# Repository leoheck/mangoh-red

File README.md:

# MangOH Red

[MangOH Red](https://mangoh.io/mangoh-red-resources) board was build using Mentor DxDesigner for schematics and Pantheon PCB for layouts. This project aims to build a version using the GREAT [Kicad](http://kicad-pcb.org/) and [FreeCad](https://www.freecadweb.org/) with [StepUp](http://kicad-pcb.org/external-tools/stepup/) plugin for Kicad.

_This project is a work in progress._

Current status
- [x] [Schematics](https://github.com/leoheck/mangoh-red/blob/master/mangoh-red.pdf)
- [x] Footprint associations (100%)
- [ ] Fix some footprints (80%)
- [x] Footprint placement (100%)
- [x] 3D models associations (90%)
- [ ] Missing 3D models creation
- [x] PCB form factor
- [ ] Routing
- [x] Bill of materials
- [ ] GERBERS

Current board and 3d view

*Feel free to help me with a PR :)*

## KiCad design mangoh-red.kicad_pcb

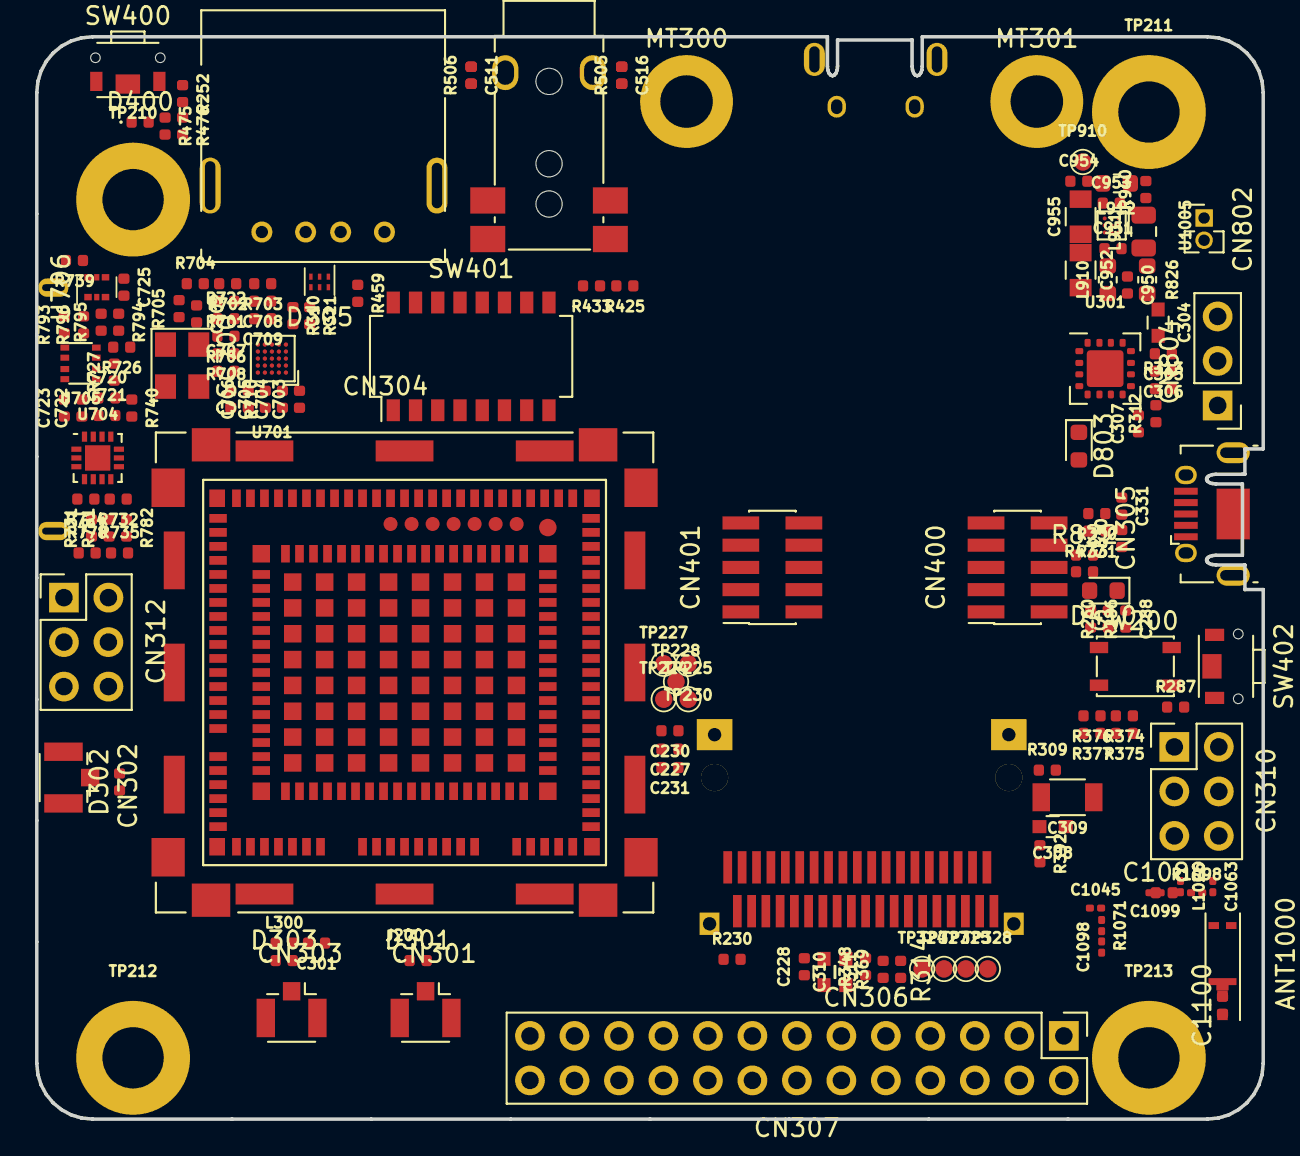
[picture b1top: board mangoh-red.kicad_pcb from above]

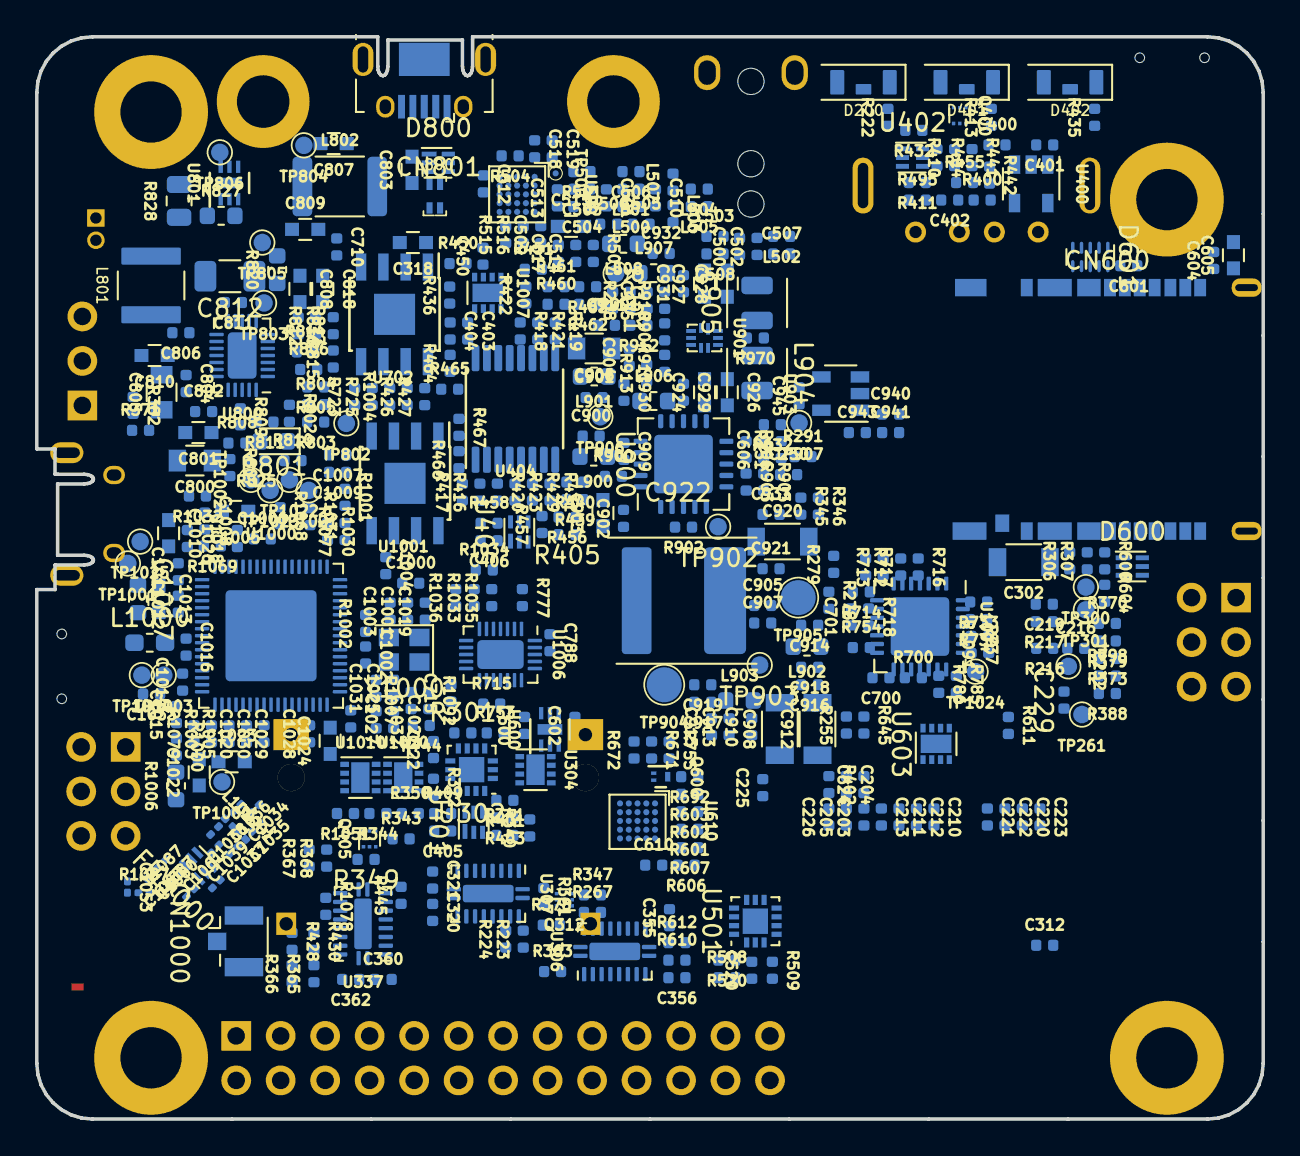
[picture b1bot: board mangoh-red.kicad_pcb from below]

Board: 6 copper layers, 70.0 x 61.8 mm, 598 parts (443 on the bottom side), 364 nets, no tracks yet.

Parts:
ANT1000: WLA.01
C203, C204, C205, C210, C211, C212, C213, C220, C221, C222, C223, C225, C226, C227, C228, C229, C230, C231, C312, C507, C508: 22p; C_0402_1005Metric
C216, C219: 12p; C_0402_1005Metric
C250, C606: 1n; C_0402_1005Metric
C288, C305, C307, C320, C321, C322, C355, C356, C360, C362, C400, C401, C402, C403, C404, C405, C406, C450, C517, C518, C520, C604, C610, C624, C700, C701, C702, C704, C705, C715, C720, C721, C722, C723, C725, C900, C901, C902, C904, C905, C907, C910, C913, C914, C915, C916, C917, C918, C919, C921, C929, C930, C931, C932, C933, C940, C941, C950, C951, C953, C954, C1000, C1003, C1007, C1012, C1014, C1020: 100n; C_0402_1005Metric
C301: 15p; C_0402_1005Metric
C302, C309, C908, C912, C920: 47u; C_1206_3216Metric
C304: 1u; C_0603_1608Metric
C306, C509, C512, C513, C514, C519, C703, C706, C707, C708, C709, C788, C1008, C1009, C1025: 4.7u; C_0402_1005Metric
C308, C605, C810: 4.7u; C_0603_1608Metric
C310, C311, C318, C803, C808, C818, C903, C1005, C1013, C1017: 10u; C_0603_1608Metric
C330, C331: 47p; C_0402_1005Metric
C500, C501, C502, C505, C506, C510, C511, C516, C1006, C1019, C1026, C1030, C1033: 100p; C_0402_1005Metric
C503, C504, C600, C601, C602, C710, C802, C804, C943, C945, C1011, C1016, C1018, C1021, C1032: 1u; C_0402_1005Metric
C515, C1010, C1022, C1023, C1024: 2.2u; C_0603_1608Metric
C800: 22u; C_0805_2012Metric
C801, C807, C809: 220n; C_0603_1608Metric
C805, C906, C952, C955: 10u; C_0805_2012Metric
C806, C909: 47n; C_0402_1005Metric
C811: 10u; C_0402_1005Metric
C812: 10u; C_1206_3216Metric
C911: 10n; C_0402_1005Metric
C922: 1.5m; CAP_2P_0720x0630_POL_NIB
C924, C926, C927, C928: 22u; C_0603_1608Metric
C925: 56p; C_0402_1005Metric
C1001, C1004: 470n; C_0402_1005Metric
C1002, C1027, C1028, C1029, C1031, C1100: 10p; C_0402_1005Metric
C1015: 470p; C_0402_1005Metric
C1034: 1p; C_0201_0603Metric
C1035, C1036, C1039, C1053, C1065: 1.5p; C_0201_0603Metric
C1037, C1038: 1.8p; C_0201_0603Metric
C1045, C1063, C1098, C1099: 10p; C_0201_0603Metric
C1060: 2.7p; C_0201_0603Metric
C1061: 100p; C_0201_0603Metric
C1087: 2.2p; C_0201_0603Metric
C1088: 10k; R_0402_1005Metric
CN301, CN302, CN303, CN1000: uFL; CONN_3P_0300x0310_RF_HIROSE
CN304: USB_A; CONN_4P_1450x1400_USB_2GND_RA_THRU
CN305, CN801: USB_B_Micro; CONN_5P_0750x0560_USB_5GND_HRS_ZX62RD
CN306: Conn_02x19_Counter_Clockwise; CONN_38P_1820x1150_0080CC_EVERCLEAR
CN307: Conn_02x13_Odd_Even; CONN_26P_3300x0483_0254CC_HEADER_THRU
CN310, CN312: Conn_02x03_Odd_Even; CONN_6P_0760x0510_HEADER_THRU_0254CC
CN400, CN401: Conn_02x05_Odd_Even; CONN_10P_0673x0305_0127CC_SMT
CN500: JP036-RT3B4AB; CONN_6P_1480x0640_AUDIO_JACK_DUAL
CN600: CN600; CONN_25P_1780x1290_0088CC_MICROSDSIM
CN802: Conn_01x02; CONN_2P_0590x0450_0200CC_THRU_HEADER
CN804: Conn_01x03; CONN_3P_0762x0254_VERTICAL_HEADER_SINGLE_ROW_THRU_SAMTEC_TSW
D200, D401, D402: LED_PAD; 12-21SYGC_S530-E2_TR8
D301, D302, D303: 0.05p; LED_0402_1005Metric
D305, D800: TPD4S012DRYR; DFN_6P_0145x0100_0050CC
D400: D_TVS; LED_0402_1005Metric
D410, D801, D803: LED; LED_0603_1608Metric
D600: RCLAMP0503N; DFN_6P_0145x0100_0050CC
D601: TPD6E004RSER; QFN_8P_0150x0150_0050CC
FIL1000: BL1608-05A2450TB; FIL_6P_0160x0080_0050CC_MURATA
J200: CF3-Socket; SIERRA_WP_SNAP-IN_BASE
L300: 47n; L_0402_1005Metric
L500, L501, L504, L505, L506, L507: 0; L_0402_1005Metric
L502, L503: 22n; L_0402_1005Metric
L508, L900, L901, L902, L903, L906, L907, L910, L912: 0; L_0603_1608Metric
L800: TCM1210-900-2P-T000; EXC24C
L801: 3.3u; IND_2P_0400x0400_0237CC_COILCRAFT
L802: 0; L_1812_4532Metric
L904, L905: 2.2u; 2016L
L911: 0; L_0805_2012Metric
L1000: 2.2u; L_0603_1608Metric_Pad1.05x0.95mm_HandSolder
L1001, L1002: 1.2n; L_0201_0603Metric
L1026: 2.2n; L_0201_0603Metric
L1087: 2.4n; L_0201_0603Metric
MT300, MT301: Round_Standoff_M2; STANDOFF_0530_0300H_THRU
OSC700: ENE3687A; Crystal_SMD_SeikoEpson_FA238V-4Pin_3.2x2.5mm
Q312, Q400, Q405: NSBC114YDP6T5G; SOT963_6P_0100x0080_0035CC
Q600: PDTC115EM; DFN_3P_0060x0100_0035CC
R216, R217, R223, R224, R230, R238, R252, R255, R260, R267, R278, R279, R309, R340, R341, R343, R344, R345, R346, R347, R348, R350, R363, R365, R366, R367, R368, R369, R370, R371, R373, R374, R375, R382, R392, R400, R416, R417, R418, R426, R427, R439, R440, R441, R442, R460, R461, R464, R465, R467, R475, R495, R505, R506, R507, R515, R516, R610, R611, R612, R645, R725, R732, R733, R736, R737, R739, R753, R754, R755, R778, R782, R785, R786, R793, R794, R795, R796, R798, R825, R902, R903, R940, R970, R1068, R1078, R1091, R1092: 0; R_0402_1005Metric
R222: 280; R_0402_1005Metric
R251, R291, R402, R432, R632: 100k; R_0402_1005Metric
R286, R301, R306, R312, R313, R372, R376, R377, R379, R388, R404, R411, R422, R425, R433, R436, R450, R451, R462, R463, R508, R509, R520, R671, R672, R692, R700, R701, R702, R703, R704, R705, R706, R708, R712, R713, R714, R715, R716, R717, R718, R722, R724, R726, R727, R731, R740, R744, R777, R781, R802, R803, R804, R805, R806, R807, R808, R809, R810, R811, R812, R904, R1000, R1001, R1002, R1003, R1004, R1005, R1051, R1077, R1079: 10k; R_0402_1005Metric
R287, R410, R445, R459: 100; R_0402_1005Metric
R307: 220; R_0402_1005Metric
R310, R311: 22; R_0402_1005Metric
R314, R401, R403, R455, R456, R457, R476, R601, R602, R603, R606, R607, R1033, R1034: 47k; R_0402_1005Metric
R330, R331: 27; R_0402_1005Metric
R349, R361, R378, R910: 820k; R_0402_1005Metric
R405, R413, R435, R477: 820; R_0402_1005Metric
R409, R458: 330; R_0402_1005Metric
R419, R420, R421, R423, R428, R429, R430, R431, R466: 4.7k; R_0402_1005Metric
R500, R501: 2.2k; R_0402_1005Metric
R504: 20K; R_0402_1005Metric
R600, R1035, R1036: 33; R_0402_1005Metric
R604, R813: 15k; R_0402_1005Metric
R710: 12k; R_0402_1005Metric
R723, R735, R1030, R1031, R1032, R1069: 10K; R_0402_1005Metric
R814: 150; R_0402_1005Metric
R815: 30.1k; R_0402_1005Metric
R816: 5.23k; R_0402_1005Metric
R820, R826, R827, R1006: 0; R_0603_1608Metric
R822, R901: R; R_0402_1005Metric
R828: 68m; R_0805_2012Metric
R900, R906: 33k; R_0402_1005Metric
R905: 220k; R_0402_1005Metric
R911: 360k; R_0402_1005Metric
R912, R913: 180k; R_0402_1005Metric
R1007: 36; R_0402_1005Metric
R1071, R1087: 10k; R_0201_0603Metric
R1098: 2.7p; R_0201_0603Metric
SW200: PTS810; SW_SPST_PTS810
SW400, SW402: SKTDLDE010; SW_5P_0390x0290_0280CC_THRU_2P
SW401: Conn_02x08_Counter_Clockwise; SW_16P_1128x0620_0127CC_DIP_SPST
TP210, TP211, TP212, TP213: TESTPOINT_0650_RND_0350H; Test_Point_Pad_d_0650
TP224, TP225, TP227, TP228, TP230, TP232, TP261, TP300, TP301, TP324, TP325, TP327, TP328, TP802, TP803, TP804, TP805, TP806, TP901, TP902, TP903, TP906, TP907, TP910, TP1000, TP1001, TP1002, TP1003, TP1004, TP1021, TP1022, TP1023, TP1024, TP1025: TestPoint; Test_Point_Pad_d_0100
TP500: TestPoint; Test_Point_Pad_d_0035
TP904, TP905: TestPoint; Test_Point_Pad_d_0200
U301: FT230XQ-R; QFN_16P_0400x0400_SLUG_0210x0210_0065CC
U302, U501: TS3A5018RSVR; QFN_16P_0260x0180_0040CC
U304, U1010, U1020: 74LVC2G126HD4-7; DFN_8P_0200x0100_0050CC
U306, U307, U337: FXMA108BQX; QFN_20P_0250x0450_SLUG_0115x0315_0050CC
U400: NCP303LSN30T1G; SOT23_5P_0300x0160_0095CC
U401, U402, U405: 74AUP1G08GM; DFN_6P_0145x0100_0050CC
U404: TCA9546APWR; TSSOP_16P_0500x0440_0065CC
U500: WM8944BECS_R; BGA_25P_0241x0241_0050CC_0030PD
U600: XC6223H29B9R-G; DFN_4P_0100x0100_SLUG_ROTATED_45DEG_0042x0042_0065CC
U603: ESIM; DFN_8P_0500x0600_SLUG_0420x0340_0127CC_ESIM_MODULE_MFF2
U610: TXS02612ZQSR; BGA_24P_0300x0300_0050CC_0030PD
U701: USB3503A-1-GL-TR; BGA_25P_0200x0200_0040CC_0030PD
U702: MIC2026-1YM; SOIC_8P_0490x0390_0127CC
U704: BMI160; QFN_14P_0250x0300_0050CC
U705: BMP280; DFN_8P_0250x0200_0065CC
U706: PNJ4K01F; DFN_6P_0155x0150_0050CC
U800: BQ24296RGER; QFN_24P_0400x0400_SLUG_0270x0270_0050CC
U801: LTC2942IDCB_TRMPBF; DFN_6P_0200x0300_SLUG_0135x0165_0050CC
U900: TPS7A7300; QFN_20P_0500x0500_SLUG_0320x0320_0065CC
U901: TPS62420DRC; DFN_10P_0300x0300_SLUG_0240x0165_0050CC_TI_POWERPAD
U903: XC6221A182MR; SOT23_5P_0300x0160_0095CC
U1000: MT7697; QFN_68P_0800x0800_SLUG_0550x0550_0040CC
U1001: MX25L3233FM1I-08G_TR; SOIC_8P_0490x0390_0127CC
U1004: SX1509BIULTRT; QFN_28P_0400x0400_SLUG_0265x0265_0040CC
U1005: TPS61253YFFR; BGA_9P_0130x0120_0040CC_0023PD
U1006: CP2130-F01-GM; QFN_24P_0400x0400_SLUG_0270x0270_0050CC
U1007: 24AA32AF-I-MNY; DFN_8P_0200x0300_SLUG_0140x0140_0050CC
Y1000: CT2520DB26000C0FZZA1; XTAL_4P_0250x0200

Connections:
2G_TX_ON: J200.60, Q400.5
/3. RF, USB, IOT connectors/CTS_FTDI: U301.4, U302.10
/3. RF, USB, IOT connectors/RTS_FTDI: U301.16, U302.2
/3. RF, USB, IOT connectors/RX_FTDI: U301.2, U302.5
/3. RF, USB, IOT connectors/TX_FTDI: U301.15, U302.7
/3. RF, USB, IOT connectors/UART2_CTS_3V3: U302.12, U307.12
/3. RF, USB, IOT connectors/UART2_RX_3V3: U302.3, U307.14
/10. WIFI and BT/WF_RF_2G_TRX_N: C1034.2, C1036.1, L1002.2, U1000.63
/10. WIFI and BT/WF_RF_2G_TRX_P: C1034.1, C1035.2, L1001.2, U1000.64
ADC0: CN306.20, R230.1
ADC1: J200.24, R370.1, R379.2
ADC1_WIFI: R374.1, R376.2, U1000.47
ADC2: J200.107, R373.2, R388.2, R798.1
ADC2_WIFI: R375.1, R377.2, U1000.46
ADC3: J200.108, R735.1, R778.1, R798.2
BATT_TS+: R815.2, R816.1, SW401.5, TP802.1, U800.11
BAT_RTC: J200.21, R306.2
BOARD_REV1: R712.2, R716.1, U1004.27
BOARD_REV2: R713.2, R717.1, U1004.28
BOARD_REV3: R714.1, R718.2, U1004.1
BattChrgr_INT_N: R785.1, R802.1, U800.7
CARD1_DETECT: C606.2, J200.64, R632.2
CARD2_DETECT: C250.2, CN312.6, J200.65, R251.2, R291.1
CARD_DETECT_IOT0: CN306.31, J200.105, R314.1
CONS_DIR: R372.1, SW401.6, U302.15, U1004.22
Charger_I2C_CLK: R427.2, U800.5, U801.3
Charger_I2C_DATA: R426.2, U800.6, U801.4
Expansion1_I2C_CLK: R421.2, U404.10, U1004.25
Expansion1_I2C_DATA: R419.2, U404.9, U1004.24
GND: ANT1000.1, C203.2, C204.2, C205.2, C210.2, C211.2, C212.2, C213.2, C216.2, C219.2, C220.2, C221.2, C222.2, C223.2, C225.2, C226.2, C227.2, C228.2, C229.2, C230.2, C231.2, C250.1, C288.2, C302.1, C304.1, C305.1, C306.1, C307.1, C308.1, C309.1, C310.1, C311.1, C312.1, C318.1, C320.1, C321.1, C322.1, C330.1, C331.2, C355.1, C356.2, C360.1, C362.1, C400.2, C401.2, C402.2, C403.2, C404.2, C405.2, C406.2, C450.2, C500.1, C502.1, C505.1, C506.1, C507.1, C508.1, C509.1, C511.1, C512.1, C513.1, C514.1, C515.1, C516.1, C517.1, C518.1, C519.1, C520.1, C600.2, C601.2, C602.2, C604.1, C605.2, C606.1, C610.2, C624.1, C700.1, C701.2, C702.1, C703.1, C704.2, C705.1, C706.2, C707.2, C708.2, C709.2, C710.2, C715.1, C720.2, C721.2, C722.2, C723.2, C725.2, C788.1, C803.2, C807.2, C809.2, C810.1, C900.2, C901.2, C902.2, C903.2, C904.2, C905.2, C906.2, C907.2, C908.2, C909.1, C910.2, C911.2, C912.2, C913.2, C914.2, C915.2, C916.2, C917.2, C918.2, C919.2, C920.2, C921.2, C922.2, C924.2, C927.2, C928.2, C929.2, C930.2, C931.2, C932.2, C933.2, C940.2, C941.2, C943.2, C945.2, C950.2, C951.2, C952.2, C953.2, C954.2, C955.2, C1000.1, C1001.1, C1002.1, C1003.1, C1004.1, C1005.1, C1006.1, C1007.2, C1008.1, C1009.2, C1010.1, C1011.1, C1013.1, C1014.1, C1015.1, C1016.2, C1017.1, C1018.2, C1019.2, C1020.1, C1021.2, C1022.1, C1023.1, C1024.1, C1025.2, C1026.2, C1027.2, C1028.2, C1029.2, C1030.2, C1031.2, C1032.2, C1033.2, C1035.1, C1036.2, C1037.1, C1038.2, C1045.2, C1053.2, C1060.2, C1061.1, C1063.2, C1065.2, C1087.2, C1098.2, C1100.2, CN301.2, CN301.3, CN302.2, CN302.3, CN303.2, CN303.3, CN304.4, CN304.5, CN305.5, CN305.6, CN306.4, CN306.21, CN306.30, CN306.38, CN307.6, CN307.9, CN307.14, CN307.20, CN307.25, CN400.3, CN400.5, CN401.3, CN401.5, CN600.G1, CN600.G2, CN600.G3, CN600.G4, CN600.G5, CN600.G6, CN600.G7, CN600.G8, CN600.S5, CN600.T6, CN801.5, CN801.6, CN802.2, CN1000.2, D301.2, D302.2, D303.2, D305.4, D400.2, D601.8, D800.4, D803.1, FIL1000.5, J200.30, J200.32, J200.37, J200.39, J200.48, J200.50, J200.67, J200.68, J200.69, J200.70, J200.111, J200.113, J200.125, J200.128, J200.136, J200.139, J200.167, J200.168, J200.169, J200.170, J200.171, J200.172, J200.173, J200.174, J200.175, J200.176, J200.177, J200.178, J200.179, J200.180, J200.181, J200.182, J200.183, J200.184, J200.185, J200.186, J200.187, J200.188, J200.189, J200.190, J200.191, J200.192, J200.193, J200.194, J200.195, J200.196, J200.197, J200.198, J200.199, J200.200, J200.201, J200.202, J200.203, J200.204, J200.205, J200.206, J200.207, J200.208, J200.209, J200.210, J200.211, J200.212, J200.213, J200.214, J200.215, J200.216, J200.217, J200.218, J200.219, J200.220, J200.221, J200.222, J200.223, J200.224, J200.225, J200.226, J200.227, J200.228, J200.229, J200.230, J200.231, J200.232, J200.233, J200.234, J200.G1, J200.G2, J200.G3, J200.G4, J200.G5, J200.G6, J200.G7, J200.G8, J200.G9, J200.G10, J200.G11, J200.G12, J200.G13, J200.G14, J200.G15, J200.G16, J200.G17, J200.G18, J200.G19, J200.G20, L1026.2, MT300.1, MT301.1, OSC700.2, Q312.1, Q312.4, Q400.1, Q400.4, Q405.1, Q405.4, Q600.2, R287.1, R291.2, R301.2, R313.2, R372.2, R376.1, R377.1, R379.1, R388.1, R401.2, R402.2, R416.1, R418.1, R422.2, R425.2, R432.2, R433.2, R436.2, R456.2, R501.1, R504.2, R505.2, R506.2, R508.2, R671.2, R703.2, R705.2, R710.2, R714.2, R716.2, R717.2, R722.2, R724.2, R726.2, R735.2, R744.1, R804.1, R806.1, R808.1, R813.1, R814.1, R815.1, R906.2, R912.1, R913.1, R970.1, R1001.1, R1002.1, R1003.1, R1005.1, R1031.2, R1032.1, R1051.2, R1079.2, SW400.1, SW400.3, SW401.16, SW402.2, TP210.1, TP211.1, TP212.1, TP213.1, TP301.1, U301.3, U301.13, U301.17, U302.6, U304.4, U306.10, U306.21, U307.10, U307.21, U337.10, U337.21, U400.3, U401.3, U402.3, U404.8, U405.3, U500.C2, U501.6, U600.2, U600.5, U603.1, U603.9, U610.C3, U610.D3, U701.C3, U702.6, U704.6, U704.7, U705.1, U705.7, U706.2, U706.3, U706.4, U800.25, U801.2, U900.8, U900.18, U900.21, U901.8, U903.2, U1000.41, U1000.42, U1000.69, U1001.4, U1004.3, U1004.10, U1004.17, U1004.26, U1004.29, U1005.C1, U1005.C2, U1005.C3, U1006.2, U1006.25, U1007.4, U1010.4, U1020.4
GPIO1|I2C1_CLK: R345.2, R461.1, R516.2, R795.1, U404.14, U705.4, U1007.6
GPIO5|I2C1_DATA: R346.2, R460.1, R515.2, U404.15, U705.3, U1007.5
GPIOEXP_INT1: J200.104, R700.1, U1004.9
GPIO_0_EXP: CN310.5, U1000.57
GPIO_1_EXP: CN310.2, U1000.56
GPIO_EXP_RPI_1: CN307.16, U1004.2
GPIO_EXP_RPI_2: CN307.18, U1004.5
GPIO_EXP_RPI_3: CN307.22, U1004.8
GPIO_IOT0_RESET: J200.10, R341.1, R401.1, R403.2, R405.1, R411.2, R456.1, R457.2, R467.1, U401.1, U401.2, U402.4, U405.1, U405.2, U701.E3, U1004.23
GPIO_WIFI_RESET: J200.159, R405.2
Generic_Push_Button: R260.1, U1004.21
HL_MODE: R404.1, SW401.4
HSIC_DATA: J200.14, U701.E2
HSIC_STRB: J200.15, U701.E1
Hub_I2C_CLK: R440.2, U701.E5
Hub_I2C_DATA: R439.2, U701.D5
IOT0_GPIO1: C229.1, C231.1, CN306.24, J200.109
IOT0_GPIO2: C203.1, CN306.25, J200.44
IOT0_GPIO3: C210.1, C228.1, CN306.26, CN401.4, J200.40
IOT0_GPIO4: C212.1, CN306.27, CN401.2, J200.41
IOT0_SCL: CN306.23, R423.2, U404.5
IOT0_SDA: CN306.22, R420.2, U404.4
LED_CARD_DETECT_IOT0: Q400.2, R255.2, R786.1
LowPower_RESET: C204.1, J200.46, R402.1, SW401.8
MIC+: C501.2, C504.1, L500.1, R500.2
MIC-: C501.1, C503.1, L501.1, R501.2
MTK_TO_WP_UART_EN: R301.1, R753.1, U302.13, U304.1, U304.7
unnamed: ANT1000.2, C1063.1, R1098.2
unnamed: ANT1000.3, C1100.1
unnamed: C288.1, R260.2, R286.2, SW200.1, SW200.2
unnamed: C301.1, CN303.1, D303.1, L300.2
unnamed: C302.2, R306.1, R307.1
unnamed: C307.2, R312.1, U301.1, U301.8
unnamed: C330.2, CN305.3, R330.2
unnamed: C331.1, CN305.2, R331.1
unnamed: C401.1, U400.5
unnamed: C503.2, U500.B3
unnamed: C504.2, U500.B4
unnamed: C505.2, C510.2, L500.2, L505.1, L506.1
unnamed: C506.2, C510.1, L501.2, L504.1, L507.1
unnamed: C507.2, CN500.4, L502.2
unnamed: C508.2, CN500.1, L503.2
unnamed: C511.2, CN500.5, L504.2, L505.2, R506.1
unnamed: C513.2, U500.A3
unnamed: C514.2, C517.2, L508.1, R507.1, U500.B5
unnamed: C515.2, U500.A4
unnamed: C516.2, CN500.6, L506.2, L507.2, R505.1
unnamed: C518.2, C519.2, R507.2, U500.A1
unnamed: C708.1, C709.1, U701.D3
unnamed: C720.1, C721.1, R740.2, R782.2, U704.5, U704.8, U704.12
unnamed: C725.1, R739.1, U706.1
unnamed: C788.2, U1006.16
unnamed: C803.1, CN801.1, CN804.3
unnamed: C804.2, C805.1, U800.23
unnamed: C806.1, U800.21
unnamed: C806.2, L801.1, U800.19, U800.20
unnamed: C902.1, C903.1, L900.2, R900.2, R902.2, U900.15, U900.16, U900.17
unnamed: C904.1, C906.1, L901.2, R904.1, U901.3
unnamed: C909.2, U900.13
unnamed: C911.1, R901.2, R970.2, U901.7, U901.9, U1005.B3
unnamed: C924.1, C926.1, C929.1, L904.2, L906.1, R911.2, U901.4
unnamed: C925.1, C927.1, C928.1, C931.1, L905.2, L907.1, R910.2
unnamed: C925.2, R910.1, R912.2, U901.1
unnamed: C926.2, R911.1, R913.2, U901.5
unnamed: C951.1, C952.1, L910.2, L911.2, U1005.A3
unnamed: C953.1, L912.1, R940.1, U1005.A1, U1005.A2
unnamed: C1002.2, U1000.4
unnamed: C1012.2, U1000.38
unnamed: C1037.2, C1039.1, FIL1000.3, L1001.1
unnamed: C1038.1, C1039.2, FIL1000.4, L1002.1
unnamed: C1045.1, C1099.2, R1071.2
unnamed: C1053.1, C1088.2, C1099.1, R1087.1
unnamed: C1060.1, FIL1000.1, L1087.2
unnamed: C1065.1, C1087.1, L1087.1, R1087.2
unnamed: C1088.1, L1026.1, R1098.1
unnamed: C1098.1, CN1000.1, R1071.1
unnamed: CN304.2, D305.1, R311.2
unnamed: CN304.3, D305.2, R310.2
unnamed: CN306.28, CN306.29, R348.2, R369.2
unnamed: CN306.32, R344.2, R350.2
unnamed: CN307.2, CN307.4, R371.2, R382.2
unnamed: CN307.3, R366.1, R367.1
unnamed: CN307.5, R365.1, R368.1
unnamed: CN307.12, R363.2
unnamed: CN310.4, R374.2
unnamed: CN310.6, R375.2
unnamed: CN312.4, R370.2
unnamed: CN600.T5, R600.2
unnamed: CN801.2, D800.1, L800.1
unnamed: CN801.3, D800.2, L800.2
unnamed: D200.1, D200.3, J200.106
unnamed: D200.2, R222.2
unnamed: D401.1, D401.3, Q400.6
unnamed: D401.2, R413.1
unnamed: D402.1, D402.3, Q400.3
unnamed: D402.2, R435.1
unnamed: D410.1, Q405.3
unnamed: D410.2, R477.1
unnamed: D801.1, R811.1, U800.4
unnamed: D801.2, R810.1
unnamed: D803.2, R822.1
unnamed: J200.1, R345.1
unnamed: J200.16, R278.2, R279.2
unnamed: J200.22, R217.2
unnamed: J200.23, R216.2
unnamed: J200.25, R230.2
unnamed: J200.45, R238.1
unnamed: J200.66, R346.1
unnamed: J200.91, R252.1
unnamed: J200.98, R224.1
unnamed: J200.99, R223.1
unnamed: J200.110, TP261.1
unnamed: J200.147, R255.1, R267.1
unnamed: J200.152, TP230.1
unnamed: J200.153, TP225.1
unnamed: J200.154, TP228.1
unnamed: J200.155, TP224.1
unnamed: J200.156, TP227.1
unnamed: L904.1, U901.6
unnamed: L905.1, U901.10
unnamed: L911.1, U1005.B1, U1005.B2
unnamed: L1000.1, U1000.40
unnamed: OSC700.3, U701.B3
unnamed: Q312.2, R347.2
unnamed: Q312.3, R378.2, U306.11
unnamed: Q312.5, R340.1, R341.2
unnamed: Q312.6, R361.2, U307.11
unnamed: Q405.2, R343.2
unnamed: Q405.6, R349.2, U337.11
unnamed: R216.1, TP232.1
unnamed: R307.2, TP300.1
unnamed: R312.2, R313.1, U301.9
unnamed: R400.1, U400.2
unnamed: R409.2, U401.4
unnamed: R416.2, U404.2
unnamed: R417.2, U404.1
unnamed: R418.2, U404.13
unnamed: R422.1, R451.2, U1007.7
unnamed: R425.1, SW401.10
unnamed: R426.1, R431.2, R440.1, U404.7
unnamed: R427.1, R429.2, R439.1, U404.6
unnamed: R433.1, SW401.12
unnamed: R436.1, U1007.2, U1007.3
unnamed: R441.1, R442.2, U400.1
unnamed: R450.2, U1007.1
unnamed: R458.2, U405.4
unnamed: R459.2, SW401.15
unnamed: R466.2, R467.2, U404.3
unnamed: R495.2, SW401.13
unnamed: R504.1, U500.C1
unnamed: R508.1, R520.2, U501.13
unnamed: R515.1, U500.C3
unnamed: R516.1, U500.C4
unnamed: R610.2, R612.2, U610.C4
unnamed: R611.2, U603.3
unnamed: R645.1, U603.6
unnamed: R701.2, U701.C5
unnamed: R702.2, R703.1, U701.E4
unnamed: R704.2, R705.1, U701.D4
unnamed: R706.2, R722.1, U701.B5
unnamed: R710.1, U701.A4
unnamed: R723.1, U702.1, U702.4
unnamed: R724.1, R731.2, R781.2, U704.1
unnamed: R725.2, U702.2, U702.3
unnamed: R726.1, R727.2, U705.5
unnamed: R732.2, R737.2, U704.4
unnamed: R733.2, R736.2, U704.9
unnamed: R753.2, U1004.6
unnamed: R754.2, U1004.7
unnamed: R755.2, U1004.14
unnamed: R777.2, U1006.19
unnamed: R778.2, U706.6
unnamed: R785.2, R786.2, U1004.13
unnamed: R793.2, R795.2, U704.13
unnamed: R794.2, R796.2, U704.14
unnamed: R803.1, R804.2, U800.8
unnamed: R805.1, R806.2, U800.9
unnamed: R807.1, R808.2, R825.1, U800.2
unnamed: R809.1, U800.3
unnamed: R812.1, R813.2, U800.12
unnamed: R814.2, U800.10
unnamed: R827.2, TP803.1
unnamed: R900.1, U900.14
unnamed: R903.2, U900.2
unnamed: R904.2, U901.2
unnamed: R905.2, R906.1, U900.3
unnamed: R1005.2, U1000.55
unnamed: R1030.1, R1031.1, U1000.20
unnamed: R1032.2, R1069.2, U1000.33
unnamed: R1035.2, U1006.23
unnamed: R1036.2, U1006.1
unnamed: R1068.2, R1078.2, U1000.45
unnamed: R1091.1, U1000.5
unnamed: R1092.1, U1000.6
unnamed: TP500.1, U500.A2
unnamed: TP806.1, U801.5
unnamed: TP1021.1, U1000.21
unnamed: TP1022.1, U1000.22
unnamed: TP1023.1, U1000.23
unnamed: TP1024.1, U1000.44
unnamed: TP1025.1, U1000.35
OSC_N: R708.2, R725.1, U701.B4
PCM_CLK: C221.1, J200.36, U501.7
PCM_CLK_CODEC: U500.D1, U501.8
PCM_CLK_IOT: CN306.36, U501.9
PCM_EXP1_SEL: R509.2, U501.15, U1004.20
PCM_IN: C220.1, J200.34, U501.10
PCM_IN_CODEC: U500.E4, U501.11
PCM_IN_IOT: CN306.33, U501.12
PCM_OUT: C223.1, J200.33, U501.5
PCM_OUT_CODEC: U500.D3, U501.4
PCM_OUT_IOT: CN306.34, U501.3
PCM_SYNC: C222.1, J200.35, U501.2
PCM_SYNC_Codec: U500.D2, U501.1
PPS: C211.1, CN306.37, J200.42
PWM_OUT: C213.1, J200.43, U306.8
PWM_OUT_3V3: R363.1, U306.13
PWR_GND_BQ: C800.1, C801.1, C802.1, C804.1, C805.2, C808.1, C811.1, C812.2, C818.2, U800.17, U800.18
PWR_ON: J200.59, SW401.1, SW402.1
Power_Fail_Indicator: R442.1, R455.1, U1004.15
RESET_IN: C400.1, D400.1, R410.2, R441.2, R475.1, SW400.2, U402.1
RESET_IN_CF3: CN401.10, J200.11, R344.1, R410.1, R445.2
RESET_IOT0: R350.1, R409.1
RESET_WIFI_1V8: R458.1, R475.2, R476.2, U307.4
RESET_WIFI_3V3: CN400.10, R715.1, R744.2, R1092.2, U307.17, U1000.51, U1006.9
RFU_PIN: CN312.5, J200.19, R373.1
RF_DIV: CN302.1, D302.1, J200.31
RF_GPS: C301.2, J200.38
RF_MAIN: CN301.1, D301.1, J200.49
SCL_EXP: R365.2, R430.2, U404.12
SDA_EXP: R366.2, R428.2, U404.11
SDIO_SEL: Q600.1, R671.1, R672.2, R755.1
SDIO_SEL_LVL: Q600.3, R692.2, U610.A2
SD_CLK: J200.162, U610.D2
SD_CLK_CARD: D601.7, R600.1, U610.A5
SD_CLK_IOT: CN306.5, U610.E5
SD_CMD: J200.161, U610.C1
SD_CMD_CARD: CN600.T3, D601.6, R601.2, U610.A4
SD_CMD_IOT: CN306.6, U610.E4
SD_D0: J200.166, U610.D1
SD_D0_CARD: CN600.T7, D601.1, R607.2, U610.B5
SD_D0_IOT: CN306.10, U610.D5
SD_D1: J200.165, U610.E1
SD_D1_CARD: CN600.T8, D601.2, R606.2, U610.C5
SD_D1_IOT: CN306.9, U610.D4
SD_D2: J200.164, U610.A1
SD_D2_CARD: CN600.T1, D601.3, R603.2, U610.B3
SD_D2_IOT: CN306.8, U610.E2
SD_D3: J200.163, U610.B1
SD_D3_CARD: CN600.T2, D601.5, R602.2, U610.A3
SD_D3_IOT: CN306.7, U610.E3
SENSOR_INT1: R737.1, U1004.16
SENSOR_INT2: R736.1, U1004.19
SPI1_CLK: CN306.16, J200.53
SPI1_MISO: CN306.17, J200.52
SPI1_MOSI: CN306.18, J200.54
SPI1_MRDY: C225.1, CN306.19, J200.51
SPI2_CLK_WIFI_3V3: CN307.23, R1036.1, U1000.25
SPI2_CS1_RPI_3V3: CN307.24, U1006.21
SPI2_CS2_RPI_3V3: CN307.26, U1006.20
SPI2_MISO_WIFI_3V3: CN307.21, R1033.2, U1000.27, U1006.24
SPI2_MOSI_WIFI_3V3: CN307.19, R1034.2, R1035.1, U1000.29
SPI2_MRDY_WIFI_3V3: U1000.24, U1006.22
SPI2_SRDY_WIFI_1V8: R267.2, U306.9
SPI2_SRDY_WIFI_3V3: R777.1, R1068.1, U306.12
SPI_CLK_EXT: U1000.19, U1001.6
SPI_CS_EXT: R1001.2, R1077.1, U1000.12, U1001.1
SPI_DATA0_EXT: U1000.9, U1001.5
SPI_DATA1_EXT: U1000.10, U1001.2
SPI_DATA2_EXT: U1000.15, U1001.3
SPI_DATA3_EXT: R1004.1, U1000.18, U1001.7
SPK+: C502.2, L502.1, U500.B2
SPK-: C500.2, L503.1, U500.B1
SYSTEM_CLK: C216.1, C219.1, R217.1, U500.E1
TP1_BOOT: C205.1, C226.1, J200.47, SW401.7
UART0_RX_EXP: CN307.10, U307.18
UART0_TX_EXP: CN307.8, U307.19
UART1_CTS: J200.4, U337.4
UART1_RTS: CN306.14, CN306.15, J200.3, U337.5
UART1_RX: CN306.13, J200.6, U337.2
UART1_TX: CN306.12, J200.5, U337.3
UART2_CTS: R223.2, U307.9
UART2_RTS: R224.2, U307.8
UART2_RX: J200.97, U307.3, U307.7
UART2_TX: J200.96, U307.2, U307.6
UIM1_CLK: CN600.S3, J200.27
UIM1_DATA: CN600.S7, J200.28, R604.2
UIM1_RESET: CN600.S2, J200.29
UIM2_CLK: J200.58, R645.2
UIM2_DATA: J200.56, R611.1
UIM2_RST: J200.57, U603.7
USB_CONSOLE_D+: R330.1, U301.6
USB_CONSOLE_D-: R331.2, U301.7
USB_D+: J200.13, L800.3
USB_D-: J200.12, L800.4
USB_EXT_D+: R311.1, U701.C1
USB_EXT_D-: R310.1, U701.D1
USB_ID: CN801.4, D800.3, R252.2, R825.2
USB_IOT_D+: CN306.2, R367.2, U701.C2
USB_IOT_D-: CN306.3, R368.2, U701.D2
USB_WIFI_D+: U701.A1, U1006.3
USB_WIFI_D-: U701.B1, U1006.4
VCC: C304.2, C305.2, C306.2, C308.2, C309.2, C310.2, C311.2, C312.2, C318.2, C320.2, C321.2, C322.2, C355.2, C356.1, C360.2, C362.2, C402.1, C403.1, C404.1, C405.1, C406.1, C450.1, C509.2, C512.2, C520.2, C600.1, C601.1, C602.1, C604.2, C605.1, C610.1, C624.2, C700.2, C701.1, C702.2, C703.2, C704.1, C705.2, C706.1, C707.1, C710.1, C715.2, C722.1, C723.1, C800.2, C801.2, C802.2, C807.1, C808.2, C809.1, C810.2, C811.2, C812.1, C818.1, C900.1, C901.1, C905.1, C907.1, C908.1, C910.1, C912.1, C913.1, C914.1, C915.1, C916.1, C917.1, C918.1, C919.1, C920.1, C921.1, C922.1, C930.1, C932.1, C933.1, C945.1, C950.1, C954.1, C955.1, C1000.2, C1001.2, C1003.2, C1004.2, C1005.2, C1006.2, C1007.1, C1008.2, C1009.1, C1010.2, C1011.2, C1012.1, C1013.2, C1014.2, C1015.2, C1016.1, C1017.2, C1018.1, C1019.1, C1020.2, C1021.1, C1022.2, C1023.2, C1024.2, C1025.1, C1026.1, C1027.1, C1028.1, C1029.1, C1030.1, C1031.1, C1032.1, C1033.1, C1061.2, CN304.1, CN305.1, CN306.1, CN306.11, CN307.1, CN307.17, CN312.2, CN400.1, CN401.1, CN600.S1, CN600.T4, CN802.1, CN804.1, CN804.2, D305.6, D601.4, D800.6, FIL1000.2, J200.26, J200.55, J200.61, J200.62, J200.63, J200.157, J200.158, J200.160, L300.1, L508.2, L801.2, L802.1, L802.2, L900.1, L901.1, L902.1, L902.2, L903.1, L903.2, L906.2, L907.2, L910.1, L912.2, L1000.2, OSC700.1, OSC700.4, R222.1, R238.2, R251.1, R278.1, R279.1, R286.1, R309.1, R309.2, R314.2, R340.2, R348.1, R349.1, R361.1, R369.1, R371.1, R378.1, R382.1, R392.1, R392.2, R400.2, R403.1, R411.1, R413.2, R417.1, R419.1, R420.1, R421.1, R423.1, R428.1, R429.1, R430.1, R431.1, R435.2, R450.1, R451.1, R455.2, R457.1, R459.1, R462.2, R463.2, R464.1, R464.2, R465.1, R465.2, R466.1, R476.1, R477.2, R495.1, R500.1, R509.1, R520.1, R601.1, R602.1, R603.1, R604.1, R606.1, R607.1, R610.1, R612.1, R632.1, R672.1, R692.1, R700.2, R701.1, R702.1, R704.1, R706.1, R708.1, R712.1, R713.1, R715.2, R718.1, R723.2, R727.1, R731.1, R739.2, R740.1, R781.1, R782.1, R802.2, R803.2, R805.2, R807.2, R809.2, R810.2, R811.2, R812.2, R816.2, R820.1, R820.2, R822.2, R826.1, R826.2, R827.1, R828.1, R828.2, R901.1, R902.1, R903.1, R905.1, R940.2, R1000.2, R1004.2, R1006.1, R1006.2, R1007.1, R1007.2, R1030.2, R1033.1, R1034.1, R1069.1, R1077.2, SW401.11, SW401.14, TP804.1, TP805.1, TP901.1, TP902.1, TP903.1, TP904.1, TP905.1, TP906.1, TP907.1, TP910.1, TP1000.1, TP1001.1, TP1002.1, TP1003.1, TP1004.1, U301.10, U302.14, U304.8, U306.1, U306.20, U307.1, U307.20, U337.1, U337.20, U401.6, U402.6, U404.16, U405.6, U500.A5, U500.E2, U500.E3, U501.14, U600.1, U600.3, U600.4, U603.8, U610.B4, U610.C2, U701.A2, U701.A3, U701.A5, U701.B2, U702.5, U702.7, U702.8, U705.2, U705.6, U705.8, U800.1, U800.13, U800.14, U800.15, U800.16, U800.22, U800.24, U801.1, U801.6, U900.1, U900.19, U900.20, U903.5, U1000.2, U1000.3, U1000.13, U1000.14, U1000.16, U1000.17, U1000.30, U1000.31, U1000.32, U1000.34, U1000.36, U1000.37, U1000.39, U1000.43, U1000.48, U1000.49, U1000.59, U1000.60, U1000.62, U1000.65, U1001.8, U1004.4, U1004.12, U1004.18, U1006.5, U1006.6, U1006.7, U1006.8, U1007.8, U1010.8, U1020.8
VCC_3V7_ULPM: C940.1, C941.1, C943.1, SW401.3, U903.1, U903.3
WIFI_GPIO00: R343.1, R347.1, R1051.1, R1091.2, U1010.1, U1010.7, U1020.1, U1020.7
WIFI_GPIO6: R1002.2, U1000.11
WIFI_HL_RESET: R1078.1, TP324.1, U337.15
WIFI_HL_RESET_1V8: R445.1, U337.6
WIFI_I2C0_CLK: CN310.3, CN400.4, R461.2, R463.1, R794.1, U1000.26
WIFI_I2C0_DATA: CN310.1, CN400.2, R460.2, R462.1, R793.1, R796.1, U1000.28
WIFI_UART0_RX: U302.8, U304.3, U1000.7
WIFI_UART0_TX: U302.4, U302.9, U304.2, U304.5, U304.6, U307.15, U1000.8
WIFI_UART1_CTS: TP328.1, U337.17, U1020.5
WIFI_UART1_CTS_MTK: U1000.50, U1020.3
WIFI_UART1_RTS: TP327.1, U337.16, U1020.6
WIFI_UART1_RTS_MTK: R1000.1, R1079.1, U1000.52, U1020.2
WIFI_UART1_RX: U337.19, U1010.5
WIFI_UART1_RX_MTK: U1000.54, U1010.3
WIFI_UART1_TX: R754.1, TP325.1, U337.18, U1010.6
WIFI_UART1_TX_MTK: R1003.2, SW401.2, U1000.53, U1010.2
WP_GPIO_1: J200.148, U306.3
WP_GPIO_1_lvl: CN307.11, U306.18
WP_GPIO_2: C227.1, J200.149, U306.4
WP_GPIO_2_lvl: CN307.13, U306.17
WP_GPIO_3: J200.150, U306.2
WP_GPIO_3_lvl: CN307.7, U306.19
WP_GPIO_4_Wakeable: CN312.1, J200.92, R732.1
WP_GPIO_5_Wakeable: CN312.3, J200.102, R733.1
WP_GPIO_7: J200.100, U306.7
WP_GPIO_7_lvl: Q405.5, U306.14
WP_GPIO_8: J200.101, U306.6
WP_GPIO_8_lvl: CN307.15, U306.15
WP_LowPower_Reset: R404.2, R432.1, SW401.9, U402.2
W_DISABLE_N: C230.1, J200.151

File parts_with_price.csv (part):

Ref;Arena Link;Category;Characteristics;Commodity Class;Created Date;Description;DXDB_LIBNAME;Effective Date;Footprint;Halogen Free;Manufacturer 1;Manufacturer 1 PN;Manufacturer 2;Manufacturer 2 PN;Manufacturer 3;Manufacturer 3 PN;Manufacturer 4;Manufacturer 4 PN;Manufacturer 5;Manufacturer 5 PN;Owner;Part Height;Part Status;Rating;Requestor;Revision;RoHS Compliant;Temperature Range;Tolerance;Value;Variant Variable Text;Voltage;Price
ANT1000;https://agiledev.sierrawireless.local/Agile/object/Parts/3015338;Antenna;;ANT - ANTENNAS;2017-01-31T19:24:40Z;ANTENNA, BLUETOOTH/WLAN/WiFi, 2.4GHz, CERAMIC CHIP, 3.2x1.6x1.1mm;Antenna;;ANT_3P_0320x0160_W3008C;N/A;TAOGLAS WLA.01;WLA.01;;;;;;;;;;1.1mm;Prototype;;Ashish Syal;1;N/A;-40 +85C;;WLA.01;;;0.0
C1000;https://app.bom.com/a/N5O6P9S9SBU5DYQF?v=files.associations;Capacitor;X7R;PAS - Passives;2008-08-21T16:59:08-08:00;CAP, 100nF, 16V, 10%, X7R, CERAMIC, 0402;Capacitor;2012-02-01T15:49:25-08:00;0402C;N/A;NIC COMPONENTS NMC0402X7R104K16TRPF;NMC0402X7R104K16TRPF;MURATA GRM155R71C104KA88D;GRM155R71C104KA88D;VISHAY VJ0402V104ZXJCW1BC;VJ0402V104ZXJCW1BC;;;;;Morris Chau;0.55mm;Production;;Airlink;2;N/A;-55 +125C;10%;100nF;;16V;0.0
C1001;https://app.bom.com/a/VDWEXH0H0J2JWE3S?v=files.associations;Capacitor;X5R;PAS - Passives;2006-01-26T19:30:31-08:00;CAP, 470nF, 6.3V, 10%, X5R, CERAMIC, 0402;Capacitor;2015-09-02T00:10:34-08:00;0402C;N/A;MURATA GRM155R60J474KE19D;GRM155R60J474KE19D;TAIYO YUDEN RM JMK105BJ474KV-F;RM JMK105BJ474KV-F;;;;;;;Morris Chau;0.55mm;Production;;Vivutha Men;1.1;N/A;-55 +85C;10%;470nF;;6.3V;0.0
C1002;https://app.bom.com/a/N5O6P9S9SBUCLHCA?v=files.associations;Capacitor;C0G;PAS - Passives;2004-12-21T10:56:53-08:00;CAP, 10pF, 50V, 5%, C0G, CERAMIC, 0402;Capacitor;2012-03-16T13:58:58-08:00;0402C;N/A;MURATA GRM1555C1H100JA01D;GRM1555C1H100JA01D;TAIYO YUDEN UMK105CG100JV-F;UMK105CG100JV-F;;;;;;;Morris Chau;0.55mm;Production;;Kevin Dotzler;2;N/A;-55 +125C;5%;10pF;DNI;50V;0.0
C1003;https://app.bom.com/a/N5O6P9S9SBU5DYQF?v=files.associations;Capacitor;X7R;PAS - Passives;2008-08-21T16:59:08-08:00;CAP, 100nF, 16V, 10%, X7R, CERAMIC, 0402;Capacitor;2012-02-01T15:49:25-08:00;0402C;N/A;NIC COMPONENTS NMC0402X7R104K16TRPF;NMC0402X7R104K16TRPF;MURATA GRM155R71C104KA88D;GRM155R71C104KA88D;VISHAY VJ0402V104ZXJCW1BC;VJ0402V104ZXJCW1BC;;;;;Morris Chau;0.55mm;Production;;Airlink;2;N/A;-55 +125C;10%;100nF;;16V;0.0
C1004;https://app.bom.com/a/VDWEXH0H0J2JWE3S?v=files.associations;Capacitor;X5R;PAS - Passives;2006-01-26T19:30:31-08:00;CAP, 470nF, 6.3V, 10%, X5R, CERAMIC, 0402;Capacitor;2015-09-02T00:10:34-08:00;0402C;N/A;MURATA GRM155R60J474KE19D;GRM155R60J474KE19D;TAIYO YUDEN RM JMK105BJ474KV-F;RM JMK105BJ474KV-F;;;;;;;Morris Chau;0.55mm;Production;;Vivutha Men;1.1;N/A;-55 +85C;10%;470nF;;6.3V;0.0
C1005;https://app.bom.com/a/6O7P8SBSBUUI7096?v=files.associations;Capacitor;X5R;PAS - Passives;2014-03-26T03:32:53-08:00;CAP, 10uF, 10V, 20%, X5R, CERAMIC, 0603;Capacitor;2014-03-26T03:37:12-08:00;0603C;N/A;MURATA GRM188R61A106ME69D;GRM188R61A106ME69D;;;;;;;;;Morris Chau;0.95mm;Design;;Mohamed Ammari;A;N/A;-55 +85C;20%;10uF;;6.3V;0.0
C1006;https://app.bom.com/a/J1K2L5O5O7OCQRFG?v=files.associations;Capacitor;C0G;PAS - Passives;2011-05-10T11:01:38-08:00;CAP, 100pF, 50V, 5%, C0G, CERAMIC, 0402;Capacitor;2014-04-28T09:22:48-08:00;0402C;;MURATA GRM1555C1H101JA01D;GRM1555C1H101JA01D;TAIYO YUDEN UMK105CG101JV-F;UMK105CG101JV-F;;;;;;;Michael Sorensen;0.55mm;Production;;Michael Sorensen;1;;-55 +125C;5%;100pF;;50V;0.0
C1007;https://app.bom.com/a/N5O6P9S9SBU5DYQF?v=files.associations;Capacitor;X7R;PAS - Passives;2008-08-21T16:59:08-08:00;CAP, 100nF, 16V, 10%, X7R, CERAMIC, 0402;Capacitor;2012-02-01T15:49:25-08:00;0402C;N/A;NIC COMPONENTS NMC0402X7R104K16TRPF;NMC0402X7R104K16TRPF;MURATA GRM155R71C104KA88D;GRM155R71C104KA88D;VISHAY VJ0402V104ZXJCW1BC;VJ0402V104ZXJCW1BC;;;;;Morris Chau;0.55mm;Production;;Airlink;2;N/A;-55 +125C;10%;100nF;;16V;0.0
C1008;https://app.bom.com/a/HZI0J3M3M55TNBEX?v=files.associations;Capacitor;X5R;PAS - Passives;2014-03-16T19:32:12-08:00;CAP, 4.7uF, 6.3V, 20%, X5R, CERAMIC, 0402;Capacitor;2014-06-06T08:29:17-08:00;0402C;N/A;MURATA GRM155R60J475ME87D;GRM155R60J475ME87D;TAIYO YUDEN JMK105BBJ475MV-F;JMK105BBJ475MV-F;;;;;;;Morris Chau;0.65mm;Production;;King Au Yeung;1;N/A;-55 +85C;20%;4.7uF;;6.3V;0.0
C1009;https://app.bom.com/a/HZI0J3M3M55TNBEX?v=files.associations;Capacitor;X5R;PAS - Passives;2014-03-16T19:32:12-08:00;CAP, 4.7uF, 6.3V, 20%, X5R, CERAMIC, 0402;Capacitor;2014-06-06T08:29:17-08:00;0402C;N/A;MURATA GRM155R60J475ME87D;GRM155R60J475ME87D;TAIYO YUDEN JMK105BBJ475MV-F;JMK105BBJ475MV-F;;;;;;;Morris Chau;0.65mm;Production;;King Au Yeung;1;N/A;-55 +85C;20%;4.7uF;DNI;6.3V;0.0
C1010;https://app.bom.com/a/UCVDWGZGZI1IUB6T?v=files.associations;Capacitor;X5R;PAS - Passives;2006-02-03T15:26:24-08:00;CAP, 2.2uF, 6.3V, 10%, X5R, CERAMIC, 0603;Capacitor;2011-12-02T13:52:33-08:00;0603C;N/A;TAIYO YUDEN CE JMK107BJ225KA-T;CE JMK107BJ225KA-T;MURATA GRM188R60J225KE19D;GRM188R60J225KE19D;;;;;;;Morris Chau;0.9mm;Production;;Mack Tan;2;N/A;-55 +85C;10%;2.2uF;;6.3V;0.0
C1011;https://app.bom.com/a/6O7P8SBSBUDMZMOD?v=files.associations;Capacitor;X5R;PAS - Passives;2009-03-11T13:25:27-08:00;CAP, 1uF, 10V, 10%, X5R, CERAMIC, 0402;Capacitor;2014-03-12T04:39:29-08:00;0402C;N/A;MURATA GRM155R61A105KE15D;GRM155R61A105KE15D;TAIYO YUDEN LMK105BJ105KV-F;LMK105BJ105KV-F;;;;;;;Morris Chau;0.55mm;Production;;Kristi Eng;2;N/A;-55 +85C;10%;1uF;;10V;0.0
C1012;https://app.bom.com/a/N5O6P9S9SBU5DYQF?v=files.associations;Capacitor;X7R;PAS - Passives;2008-08-21T16:59:08-08:00;CAP, 100nF, 16V, 10%, X7R, CERAMIC, 0402;Capacitor;2012-02-01T15:49:25-08:00;0402C;N/A;NIC COMPONENTS NMC0402X7R104K16TRPF;NMC0402X7R104K16TRPF;MURATA GRM155R71C104KA88D;GRM155R71C104KA88D;VISHAY VJ0402V104ZXJCW1BC;VJ0402V104ZXJCW1BC;;;;;Morris Chau;0.55mm;Production;;Airlink;2;N/A;-55 +125C;10%;100nF;;16V;0.0
C1013;https://app.bom.com/a/6O7P8SBSBUUI7096?v=files.associations;Capacitor;X5R;PAS - Passives;2014-03-26T03:32:53-08:00;CAP, 10uF, 10V, 20%, X5R, CERAMIC, 0603;Capacitor;2014-03-26T03:37:12-08:00;0603C;N/A;MURATA GRM188R61A106ME69D;GRM188R61A106ME69D;;;;;;;;;Morris Chau;0.95mm;Design;;Mohamed Ammari;A;N/A;-55 +85C;20%;10uF;;6.3V;0.0
C1014;https://app.bom.com/a/N5O6P9S9SBU5DYQF?v=files.associations;Capacitor;X7R;PAS - Passives;2008-08-21T16:59:08-08:00;CAP, 100nF, 16V, 10%, X7R, CERAMIC, 0402;Capacitor;2012-02-01T15:49:25-08:00;0402C;N/A;NIC COMPONENTS NMC0402X7R104K16TRPF;NMC0402X7R104K16TRPF;MURATA GRM155R71C104KA88D;GRM155R71C104KA88D;VISHAY VJ0402V104ZXJCW1BC;VJ0402V104ZXJCW1BC;;;;;Morris Chau;0.55mm;Production;;Airlink;2;N/A;-55 +125C;10%;100nF;;16V;0.0
C1015;https://app.bom.com/a/DVEWFZIZI1I6KLAM?v=files.associations;Capacitor;X7R;PAS - Passives;2011-05-10T11:00:32-08:00;CAP, 470pF, 50V, 10%, X7R, CERAMIC, 0402;Capacitor;2015-06-16T18:03:21-08:00;0402C;;MURATA GRM155R71H471KA01D;GRM155R71H471KA01D;TAIYO YUDEN UMK105BJ471KV-F;UMK105BJ471KV-F;;;;;;;Michael Sorensen;0.55mm;Production;;Michael Sorensen;1;;-55 +125C;10%;470pF;;50V;0.0
C1016;https://app.bom.com/a/6O7P8SBSBUDMZMOD?v=files.associations;Capacitor;X5R;PAS - Passives;2009-03-11T13:25:27-08:00;CAP, 1uF, 10V, 10%, X5R, CERAMIC, 0402;Capacitor;2014-03-12T04:39:29-08:00;0402C;N/A;MURATA GRM155R61A105KE15D;GRM155R61A105KE15D;TAIYO YUDEN LMK105BJ105KV-F;LMK105BJ105KV-F;;;;;;;Morris Chau;0.55mm;Production;;Kristi Eng;2;N/A;-55 +85C;10%;1uF;;10V;0.0
C1017;https://app.bom.com/a/6O7P8SBSBUUI7096?v=files.associations;Capacitor;X5R;PAS - Passives;2014-03-26T03:32:53-08:00;CAP, 10uF, 10V, 20%, X5R, CERAMIC, 0603;Capacitor;2014-03-26T03:37:12-08:00;0603C;N/A;MURATA GRM188R61A106ME69D;GRM188R61A106ME69D;;;;;;;;;Morris Chau;0.95mm;Design;;Mohamed Ammari;A;N/A;-55 +85C;20%;10uF;;6.3V;0.0
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
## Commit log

2018-08-01 Add project file
2018-08-01 Add schematics
2018-08-01 Add symbols/footprints paths
2018-08-01 Add initial layout
2018-08-01 Add library
2018-08-01 Initial board outline
2018-08-01 Fix library name
2018-08-01 Renaming step files
2018-08-01 Fix 3dparts references
2018-08-01 Add 3d model
2018-08-01 Refactor main filenames
2018-08-01 Removing files with old names
2018-08-01 Fix path to custom modules
2018-08-01 Organizing
2018-08-03 Refactor footprints
2018-08-03 Refactor footprints and paths
2018-08-03 Refactor paths
2018-08-03 Add datasheets
2018-08-03 Add testpoint footprints
2018-08-03 Updating tespoints and other parts
2018-08-03 Add initial version of missing footprints
2018-08-03 Footprint renamed
2018-08-03 Change custom footprints references
2018-08-03 Add footprint
2018-08-03 Updating
2018-08-03 Add datasheet
2018-08-03 Initial changes
2018-12-30 Add SnapEDA footprint and symbol for WP Snap In Base socket. Per SnapEDA's license, these parts are licensed as follows: "Creative Commons Attribution-ShareAlike 4.0 International License (CC BY-SA) 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
    For full license details see: https://www.snapeda.com/about/FAQ/#faq
2018-12-30 Change footprint of CF3 socket to use the one generated by SnapEDA.
2019-05-07 Footprint for WP Snap In from SnapEDA
2019-05-07 Remove old (unfinished) footprint
2019-05-07 Update the footprint of the main IC
2019-05-07 Add gitattributes to filter some kicad noise
2019-05-07 Update file versions
2019-05-07 Minor placement update
2019-05-07 Update the main component
2019-05-07 Map its 3d model to the footprint
2019-05-07 Fix snap in ic
2019-05-07 Change some pin names to match the schematic and also remove unecessary polygons
2019-05-07 Add scripts
2019-05-07 Update footprints
2019-05-07 Add MPNX field
2019-05-07 Replace MPNX partnumbers
2019-05-07 Fix some MPNs
2019-05-07 Fix some footprints
2019-05-07 Add new footprints files, they still need to inspected
2019-05-07 Update MPNs and footprints
2019-05-07 Add extra datasheets
2019-05-07 Add board to svg plugin
2019-05-07 Create svg board (back and front)
2019-05-07 Remove cache libs from gitignore
2019-05-07 Remove .gitatributes because it does not work fine anymore
2019-05-07 Add version back
2019-05-07 Fix pins position
2019-05-07 Replace wrl models by step models
2019-05-08 Many updates
2019-05-08 Add new files
2019-05-08 Improve it a little bit
2019-05-08 Save Edge.cut visible
2019-05-08 Update some footprints
2019-05-08 Many improvements
2019-05-09 Update models and parts placement
2019-05-09 Update models path
2019-05-09 Add footprint with board outline
2019-05-09 Add original placement file
2019-05-09 Some updates
2019-05-09 Skip report.txt
2019-05-09 Update footprint
2019-05-09 Add footprints and 3d models
2019-05-09 Add new footprints to fix orientation
2019-05-09 Improve orientation
2019-05-10 Update colors
2019-05-10 Update usb mini footprint
2019-05-10 Update antenna footprint
2019-05-14 Add the original outline
2019-05-18 BOM from Mangoh Board
2019-05-18 Add docs
2019-05-18 Add URL and the current price
2019-05-18 Add extra symbols for WP snap in IC and COVER.
2019-05-18 Add the missing WP7702 module
2019-05-18 Add images
2019-05-18 Add extra files
2019-05-20 Update 3d models
